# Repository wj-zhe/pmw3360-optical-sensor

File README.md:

# optical-sensor
pmw 3360 based optical sensor. Heavily inspired by Bastardkb design.

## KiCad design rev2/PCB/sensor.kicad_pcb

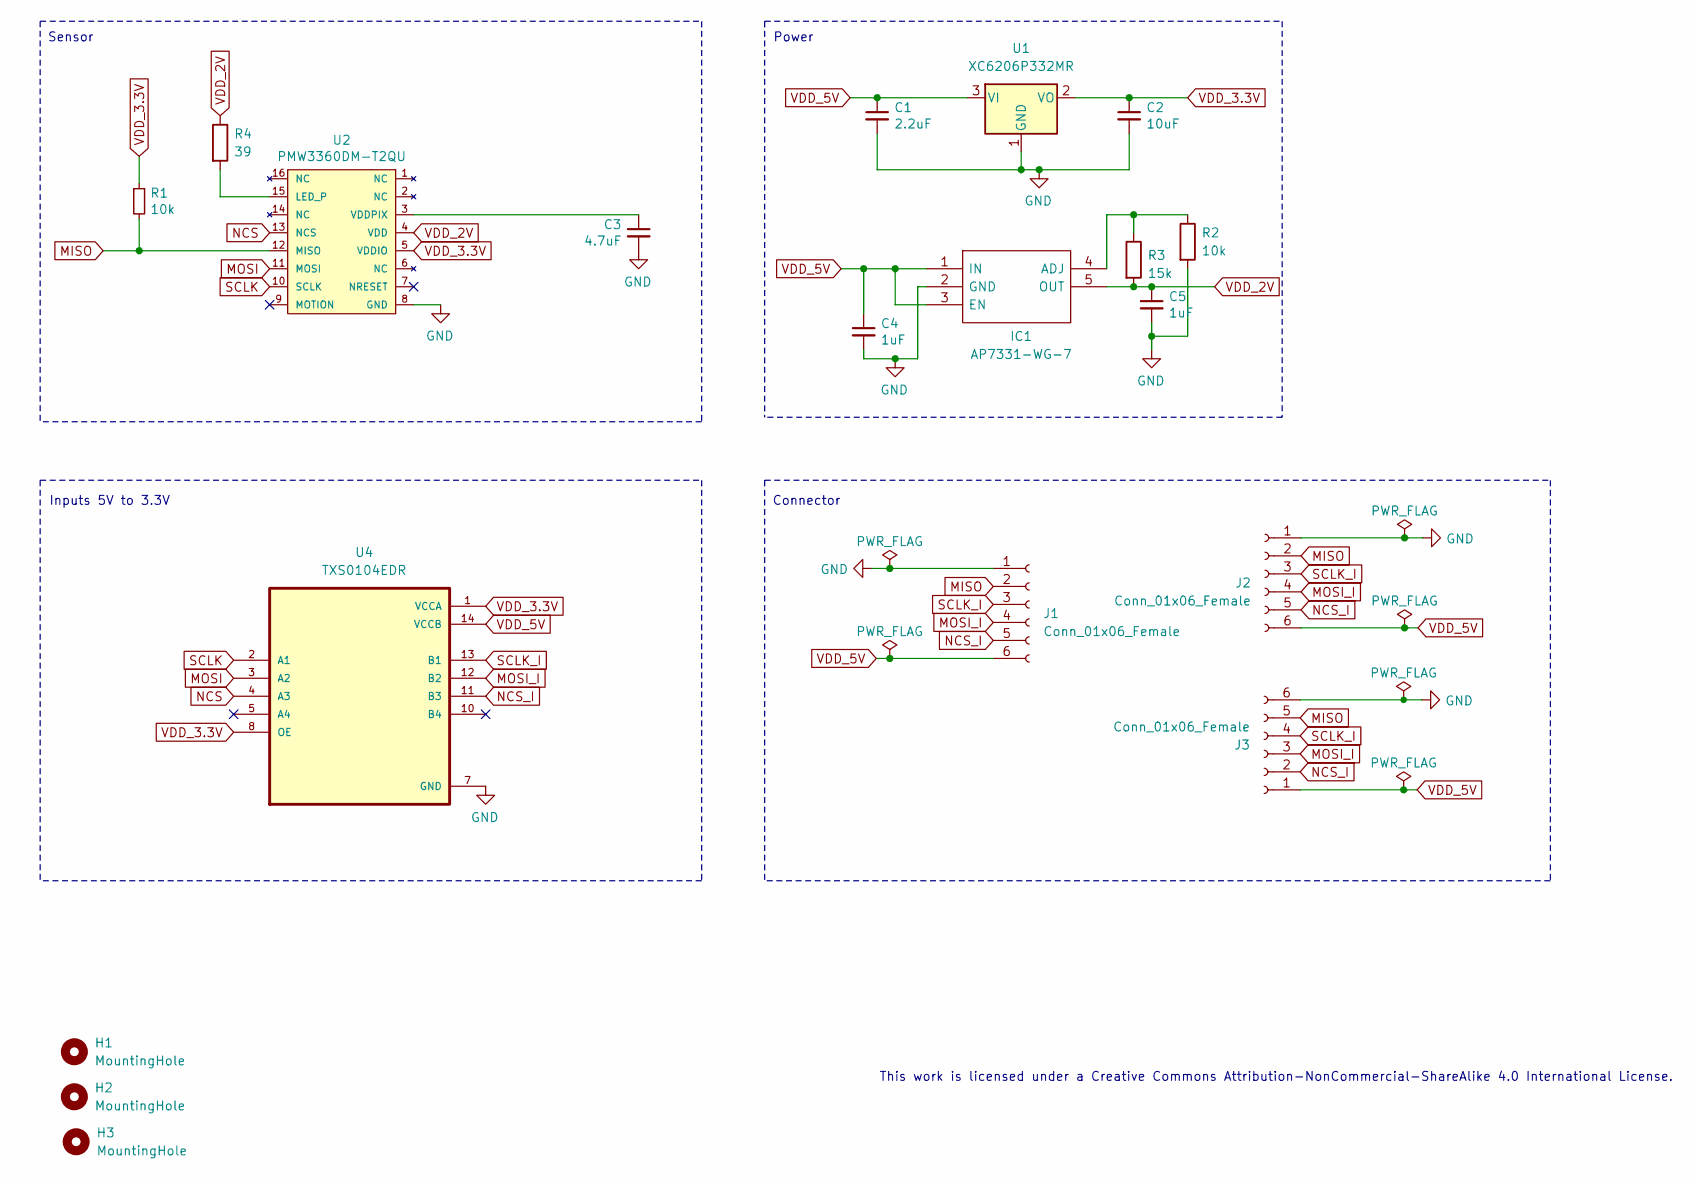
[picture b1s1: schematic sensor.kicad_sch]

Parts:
C1: 2.2uF; C_1206_3216Metric_Pad1.42x1.75mm_HandSolder; LCSC C1858
C2: 10uF; C_1206_3216Metric_Pad1.42x1.75mm_HandSolder; LCSC C152957
C3: 4.7uF; C_1206_3216Metric_Pad1.42x1.75mm_HandSolder; LCSC C29823
C4, C5: 1uF; C_1206_3216Metric_Pad1.42x1.75mm_HandSolder; LCSC C1926
H1, H2, H3: MountingHole; MountingHole_3.2mm_M3_ISO7380_Pad
IC1: AP7331-WG-7; AP7331; Manufacturer_Part_Number AP7331-WG-7; Mouser Part Number 621-AP7331-WG-7
J1: Conn_01x06_Female; Hirose_DF13-06P-1.25DS_1x06_P1.25mm_Horizontal
J2, J3: Conn_01x06_Female; TE_84952-6_1x06-1MP_P1.0mm_Horizontal
R1, R2: 10k; R_1206_3216Metric_Pad1.42x1.75mm_HandSolder; LCSC C328409
R3: 15k; R_1206_3216Metric_Pad1.42x1.75mm_HandSolder; LCSC C351534
R4: 39; R_1206_3216Metric_Pad1.42x1.75mm_HandSolder; LCSC C153384
U1: XC6206P332MR; TSOT-23_HandSoldering; LCSC C347376
U2: PMW3360DM-T2QU; PMW3360DM_DIP-16_W10.16mm
U4: TXS0104EDR; SOIC127P600X175-14N; LCSC C79342

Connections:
GND: C1.2, C2.2, C3.2, C4.2, C5.2, IC1.2 (GND), J1.1, J2.1, J3.6, R2.2, U1.1 (GND), U2.8 (GND), U4.7 (GND)
MISO: J1.2, J2.2, J3.5, R1.2, U2.12 (MISO)
MOSI: U2.11 (MOSI), U4.3 (A2)
MOSI_I: J1.4, J2.4, J3.3, U4.12 (B2)
NCS: U2.13 (NCS), U4.4 (A3)
NCS_I: J1.5, J2.5, J3.2, U4.11 (B3)
unnamed: IC1.4 (ADJ), R2.1, R3.1
unnamed: R4.2, U2.15 (LED_P)
unnamed: C3.1, U2.3 (VDDPIX)
SCLK: U2.10 (SCLK), U4.2 (A1)
SCLK_I: J1.3, J2.3, J3.4, U4.13 (B1)
VDD_2V: C5.1, IC1.5 (OUT), R3.2, R4.1, U2.4 (VDD)
VDD_3.3V: C2.1, R1.1, U1.2 (VO), U2.5 (VDDIO), U4.1 (VCCA), U4.8 (OE)
VDD_5V: C1.1, C4.1, IC1.1 (IN), IC1.3 (EN), J1.6, J2.6, J3.1, U1.3 (VI), U4.14 (VCCB)

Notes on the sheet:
This work is licensed under a Creative Commons Attribution-NonCommercial-ShareAlike 4.0 International License.
Power
Sensor
Inputs 5V to 3.3V
Connector

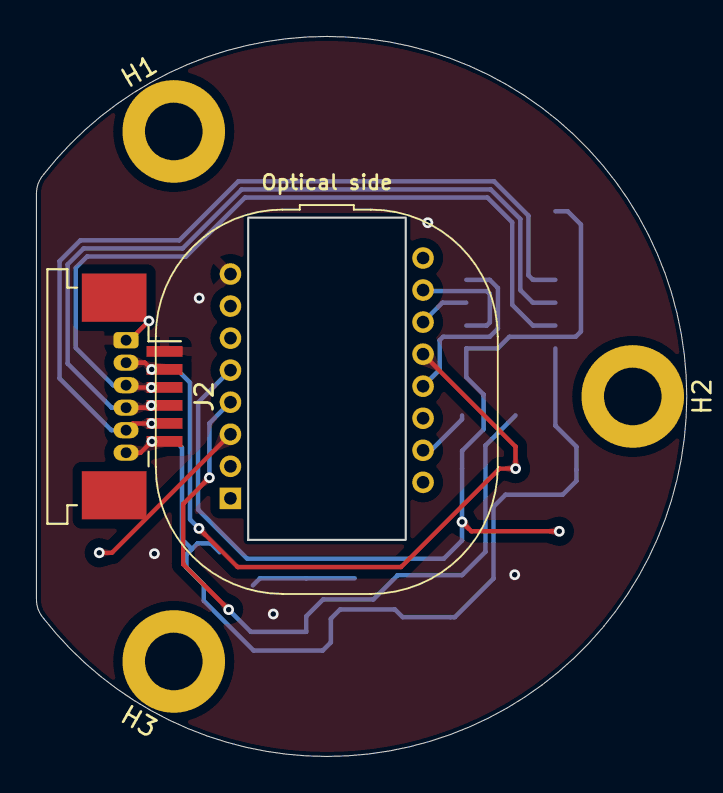
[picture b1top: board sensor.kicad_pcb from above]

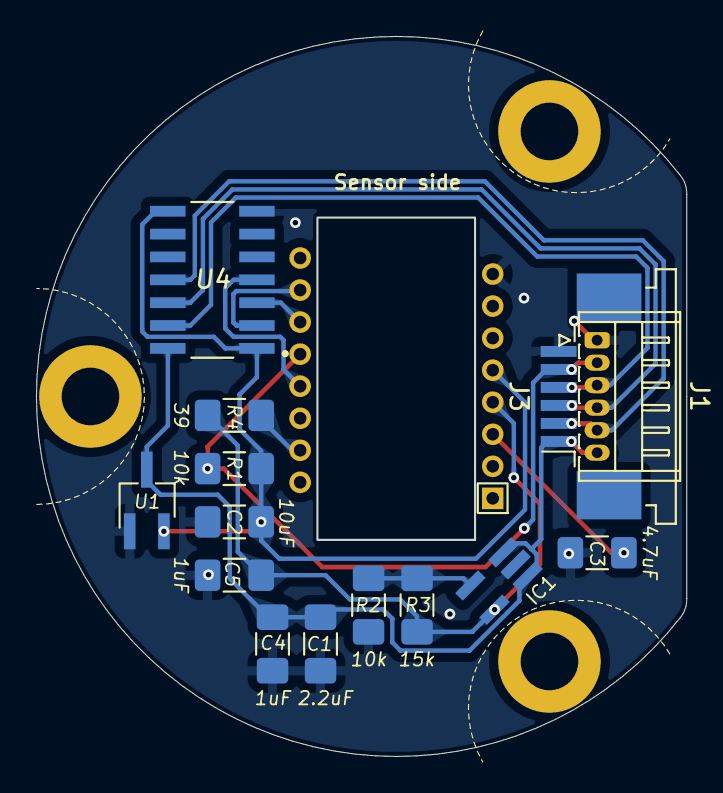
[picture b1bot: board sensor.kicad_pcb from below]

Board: 2 copper layers, 36.1 x 39.9 mm, 19 parts (15 on the bottom side), 14 nets.

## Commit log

2024-02-12 Initial upload.
2024-07-21 Making rev2

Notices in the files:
rev1/PCB/sensor.kicad_sch:
Copyright Quentin Lebastard
